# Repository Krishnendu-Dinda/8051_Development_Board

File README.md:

# 8051_Development_Board
<br>
In my college when I worked in many projects on embedded system using MCU I face many hardware related problems because of create peripherals circuit in breadboard. 
<br>
 For solved this problem I design this 8051 Development board.That is help the student to avoid many hardware related issues due to printed circuit. 
 <br>
 Here in my Development board include one 8-bit output circuit,one 8-bit input circuit, one 8-bit successive approximation A/D converter ,one 16x2 LCD circuit. and also include the programming pins.
<br> 
 It is more helpful if you all are go through the below attached my GitHub link for any advice & review my design.
 <br>

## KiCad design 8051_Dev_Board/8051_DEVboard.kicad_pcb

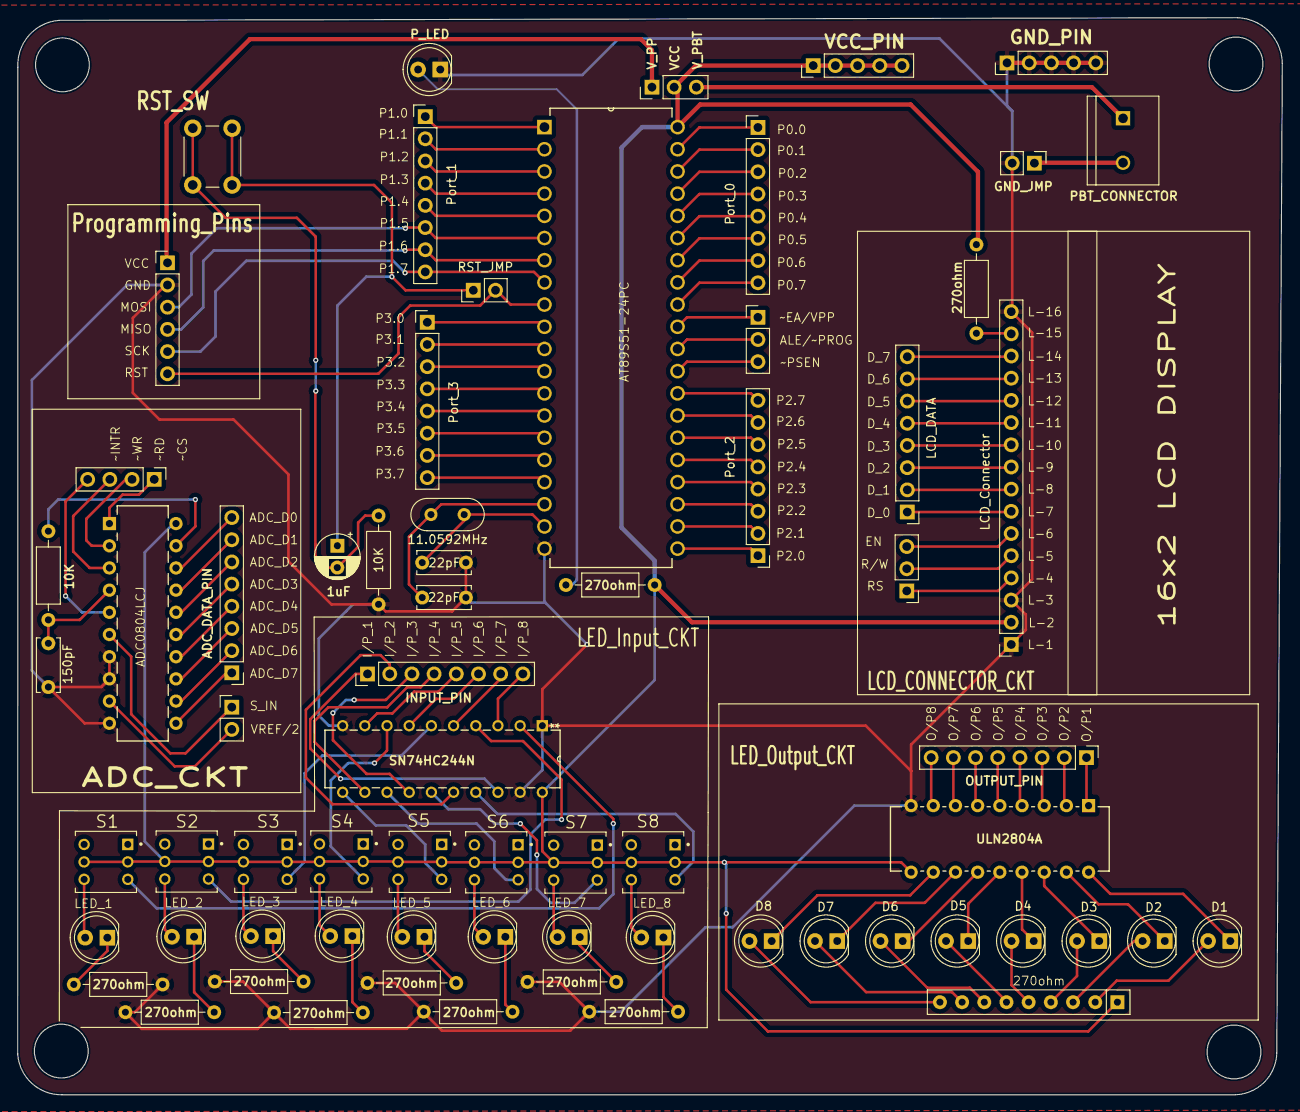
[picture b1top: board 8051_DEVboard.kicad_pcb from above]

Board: 2 copper layers, 144.8 x 123.3 mm, 69 parts (1 on the bottom side), 130 nets.

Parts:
1uF1: C_Polarized_US; CP_Radial_D5.0mm_P2.50mm
10K2, 10k1, 270ohm, 270ohm1, 270ohm2, 270ohm3, 270ohm4, 270ohm5, 270ohm6, 270ohm8, 270ohm9, 270ohm10: R_US; R_Axial_DIN0207_L6.3mm_D2.5mm_P10.16mm_Horizontal
ADC_DATA1: Conn_01x08; PinHeader_1x08_P2.54mm_Vertical
C1, C2: 22pF; C_Disc_D6.0mm_W2.5mm_P5.00mm
C3: 150pF; C_Disc_D6.0mm_W2.5mm_P5.00mm
D1, D2, D3, D4, D5, D6, D7, D8, D9, D10, D11, D12, D13, D14, D15, D16, D17: LED; LED_D5.0mm_Clear
GND_JMP1: Conn_01x02; PinHeader_1x02_P2.54mm_Vertical
J1: VCC_PBT_P; PinHeader_1x03_P2.54mm_Vertical
J2: CsRdWrIntr; PinHeader_1x04_P2.54mm_Vertical
J3, J6: Conn_01x02; PinHeader_1x02_P2.54mm_Vertical
J4: LCD_Connection; PinSocket_1x16_P2.54mm_Vertical
J5: Conn_01x03; PinHeader_1x03_P2.54mm_Vertical
J8: GND_PINS; PinHeader_1x05_P2.54mm_Vertical
J9: VCC_PINS; PinHeader_1x05_P2.54mm_Vertical
LCD_DATA1: Conn_01x08; PinHeader_1x08_P2.54mm_Vertical
OUTPUT_LED1, OUTPUT_LED2: Conn_01x08; PinHeader_1x08_P2.54mm_Vertical
PBT_CONNECTOR1: 282837-2; TE_282837-2
Port_0, Port_1, Port_2, Port_3: Conn_01x08; PinHeader_1x08_P2.54mm_Vertical
Programming_Pins1: Conn_01x06; PinHeader_1x06_P2.54mm_Vertical
RN1: 270ohm; R_Array_SIP9
RS_R/W_EN1: Conn_01x03; PinHeader_1x03_P2.54mm_Vertical
S1, S2, S3, S4, S5, S6, S7, S8: TL2230OAF140; DPST_PUSH_SWITCH
SW1: SW_Push; SW_PUSH_6mm
U1: AT89S51-24PC; DIP254P1524X482-40
U2: ULN2804A; ULN2804
U3: SN74HC244N; 74244
U4: ADC0804LCJ; DIP20_300_TEX
Y1: 11.0592MHz; Crystal_HC52-U_Vertical
logo: LOGO

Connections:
/ADC_DB0: ADC_DATA1.8 (Pin_7), U4.18 (DB0)
/ADC_DB1: ADC_DATA1.7 (Pin_6), U4.17 (DB1)
/ADC_DB2: ADC_DATA1.6 (Pin_5), U4.16 (DB2)
/ADC_DB3: ADC_DATA1.5 (Pin_4), U4.15 (DB3)
/ADC_DB4: ADC_DATA1.4 (Pin_3), U4.14 (DB4)
/ADC_DB5: ADC_DATA1.3 (Pin_2), U4.13 (DB5)
/ADC_DB6: ADC_DATA1.2 (Pin_1), U4.12 (DB6)
/ADC_DB7: ADC_DATA1.1 (Pin_0), U4.11 (DB7)
/CLKIN: 10K2.2, C3.1, U4.4 (CLKIN)
/CLKR: 10K2.1, U4.19 (CLKR)
/INT0: Port_3.3 (Pin_2), U1.12 ((INT0)_P3.2)
/INT1: Port_3.4 (Pin_3), U1.13 ((INT1)_P3.3)
/MISO: Port_1.7 (Pin_6), Programming_Pins1.4, U1.7 ((MISO)_P1.6)
/MOSI: Port_1.6 (Pin_5), Programming_Pins1.3, U1.6 ((MOSI)_P1.5)
/PBT_GND: GND_JMP1.1, PBT_CONNECTOR1.2
/PBT_VCC: J1.3, PBT_CONNECTOR1.1
/P_VCC: J1.1, Programming_Pins1.1
/RD: Port_3.8 (Pin_7), U1.17 ((RD)_P3.7)
/RST: J3.2, Programming_Pins1.6, U1.9 (RST)
/RXD: Port_3.1 (Pin_0), U1.10 ((RXD)_P3.0)
/SCK: Port_1.8 (Pin_7), Programming_Pins1.5, U1.8 ((SCK)_P1.7)
/SENSOR_IN: J6.1, U4.6 (VIN+)
/SW1_LED: D10.2 (A), S1.6
/SW2_LED: D11.2 (A), S2.6
/SW3_LED: D12.2 (A), S3.6
/SW4_LED: D14.2 (A), S4.6
/SW5_LED: D17.2 (A), S5.6
/SW6_LED: D16.2 (A), S6.6
/SW7_LED: D13.2 (A), S7.6
/SW8_LED: D15.2 (A), S8.6
/SW_1: S1.3, U3.2 (1A1)
/SW_1_out: OUTPUT_LED2.1 (Pin_0), U3.18 (1Y1)
/SW_2: S2.3, U3.4 (1A2)
/SW_2_out: OUTPUT_LED2.2 (Pin_1), U3.16 (1Y2)
/SW_3: S3.3, U3.6 (1A3)
/SW_3_out: OUTPUT_LED2.3 (Pin_2), U3.14 (1Y3)
/SW_4: S4.3, U3.8 (1A4)
/SW_4_out: OUTPUT_LED2.4 (Pin_3), U3.12 (1Y4)
/SW_5: S5.3, U3.11 (2A1)
/SW_5_out: OUTPUT_LED2.5 (Pin_4), U3.9 (2Y1)
/SW_6: S6.3, U3.13 (2A2)
/SW_6_out: OUTPUT_LED2.6 (Pin_5), U3.7 (2Y2)
/SW_7: S7.3, U3.15 (2A3)
/SW_7_out: OUTPUT_LED2.7 (Pin_6), U3.5 (2Y3)
/SW_8: S8.3, U3.17 (2A4)
/SW_8_out: OUTPUT_LED2.8 (Pin_7), U3.3 (2Y4)
/T0: Port_3.5 (Pin_4), U1.14 ((T0)_P3.4)
/T1: Port_3.6 (Pin_5), U1.15 ((T1)_P3.5)
/TXD: Port_3.2 (Pin_1), U1.11 ((TXD)_P3.1)
/VCC: 270ohm1.1, 270ohm2.1, J1.2, J4.2, J9.1, J9.2, J9.3, J9.4, J9.5, RN1.1 (common), S1.2, S1.5, S2.2, S2.5, S3.2, S3.5, S4.2, S4.5, S5.2, S5.5, S6.2, S6.5, S7.2, S7.5, S8.2, S8.5, U1.40 (VCC), U2.10 (COM), U3.20 (VCC), U4.20 (VCC)
/VREF/2: J6.2, U4.9 (VREF/2)
/WR: Port_3.7 (Pin_6), U1.16 ((WR)_P3.6)
/~CS: J2.1, U4.1 (~CS)
/~INTR: J2.4, U4.5 (~INTR)
/~RD: J2.2, U4.2 (~RD)
/~WR: J2.3, U4.3 (~WR)
GND: 10k1.2, 270ohm.1, 270ohm3.1, 270ohm4.1, 270ohm5.1, 270ohm6.1, 270ohm8.1, 270ohm9.1, 270ohm10.1, C1.1, C2.1, C3.2, D9.1 (K), GND_JMP1.2, J4.1, J4.3, J4.16, J8.1, J8.2, J8.3, J8.4, J8.5, Programming_Pins1.2, U1.20 (GND), U2.9 (GND), U3.1 (*1OE), U3.10 (GND), U3.19 (*2OE), U4.7 (VIN-), U4.8 (AGND), U4.10 (DGND)
unnamed: 1uF1.2, 10k1.1, SW1.1
unnamed: D1.2 (A), RN1.2 (R1)
unnamed: D1.1 (K), U2.18 (O1)
unnamed: D2.2 (A), RN1.3 (R2)
unnamed: D2.1 (K), U2.17 (O2)
unnamed: D3.2 (A), RN1.4 (R3)
unnamed: D3.1 (K), U2.16 (O3)
unnamed: D4.2 (A), RN1.5 (R4)
unnamed: D4.1 (K), U2.15 (O4)
unnamed: D5.2 (A), RN1.6 (R5)
unnamed: D5.1 (K), U2.14 (O5)
unnamed: D6.2 (A), RN1.7 (R6)
unnamed: D6.1 (K), U2.13 (O6)
unnamed: D7.2 (A), RN1.8 (R7)
unnamed: D7.1 (K), U2.12 (O7)
unnamed: D8.2 (A), RN1.9 (R8)
unnamed: D8.1 (K), U2.11 (O8)
unnamed: 270ohm2.2, D9.2 (A)
unnamed: 270ohm3.2, D10.1 (K)
unnamed: 270ohm4.2, D11.1 (K)
unnamed: 270ohm5.2, D12.1 (K)
unnamed: 270ohm8.2, D13.1 (K)
unnamed: 270ohm6.2, D14.1 (K)
unnamed: 270ohm.2, D15.1 (K)
unnamed: 270ohm9.2, D16.1 (K)
unnamed: 270ohm10.2, D17.1 (K)
unnamed: 1uF1.1, J3.1, SW1.2
unnamed: J4.4, RS_R/W_EN1.1
unnamed: J4.5, RS_R/W_EN1.2
unnamed: J4.6, RS_R/W_EN1.3
unnamed: J4.7, LCD_DATA1.1 (Pin_0)
unnamed: J4.8, LCD_DATA1.2 (Pin_1)
unnamed: J4.9, LCD_DATA1.3 (Pin_2)
unnamed: J4.10, LCD_DATA1.4 (Pin_3)
unnamed: J4.11, LCD_DATA1.5 (Pin_4)
unnamed: J4.12, LCD_DATA1.6 (Pin_5)
unnamed: J4.13, LCD_DATA1.7 (Pin_6)
unnamed: J4.14, LCD_DATA1.8 (Pin_7)
unnamed: 270ohm1.2, J4.15
unnamed: J5.1, U1.31 (~EA/VPP)
unnamed: J5.2, U1.30 (ALE/~PROG)
unnamed: J5.3, U1.29 (~PSEN)
unnamed: OUTPUT_LED1.1 (Pin_0), U2.1 (I1)
unnamed: OUTPUT_LED1.2 (Pin_1), U2.2 (I2)
unnamed: OUTPUT_LED1.3 (Pin_2), U2.3 (I3)
unnamed: OUTPUT_LED1.4 (Pin_3), U2.4 (I4)
unnamed: OUTPUT_LED1.5 (Pin_4), U2.5 (I5)
unnamed: OUTPUT_LED1.6 (Pin_5), U2.6 (I6)
unnamed: OUTPUT_LED1.7 (Pin_6), U2.7 (I7)
unnamed: OUTPUT_LED1.8 (Pin_7), U2.8 (I8)
unnamed: Port_0.1 (Pin_0), U1.39 (P0.0_(AD0))
unnamed: Port_0.2 (Pin_1), U1.38 (P0.1_(AD1))
unnamed: Port_0.3 (Pin_2), U1.37 (P0.2_(AD2))
unnamed: Port_0.4 (Pin_3), U1.36 (P0.3_(AD3))
unnamed: Port_0.5 (Pin_4), U1.35 (P0.4_(AD4))
unnamed: Port_0.6 (Pin_5), U1.34 (P0.5_(AD5))
unnamed: Port_0.7 (Pin_6), U1.33 (P0.6_(AD6))
unnamed: Port_0.8 (Pin_7), U1.32 (P0.7_(AD7))
unnamed: Port_1.1 (Pin_0), U1.1 ((T2)_P1.0)
unnamed: Port_1.2 (Pin_1), U1.2 ((T2_EX)_P1.1)
unnamed: Port_1.3 (Pin_2), U1.3 (P1.2)
unnamed: Port_1.4 (Pin_3), U1.4 (P1.3)
unnamed: Port_1.5 (Pin_4), U1.5 (P1.4)
unnamed: Port_2.1 (Pin_0), U1.21 (P2.0_(A8))
unnamed: Port_2.2 (Pin_1), U1.22 (P2.1_(A9))
unnamed: Port_2.3 (Pin_2), U1.23 (P2.2_(A10))
unnamed: Port_2.4 (Pin_3), U1.24 (P2.3_(A11))
unnamed: Port_2.5 (Pin_4), U1.25 (P2.4_(A12))
unnamed: Port_2.6 (Pin_5), U1.26 (P2.5_(A13))
unnamed: Port_2.7 (Pin_6), U1.27 (P2.6_(A14))
unnamed: Port_2.8 (Pin_7), U1.28 (P2.7_(A15))
unnamed: C2.2, U1.19 (XTAL1), Y1.2
unnamed: C1.2, U1.18 (XTAL2), Y1.1

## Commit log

2025-03-15 Create temp
2025-03-15 Update temp
